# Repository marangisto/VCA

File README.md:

# VCA
DIY Modular VCA

Inspired by RJWSoft's Dual Log/Linear VCA but incorporating ideas from application notes
and use of the diode bias inputs in the OTA together with supply adjustements
to ensure both exponential and linear modes can drive levels all the way to zero.

To calibrate:

1) Set offset potentiometer so that its output viper is at 0V (measure on board).

2) Adjust the 100k trimmer (bottom-most) as close to 0mV as possible at output jack.
note that during this phase you may need to mix in adjustments of the 2k trimmer
to make this feasible.

3) Feed a 100Hz 10Vpp square signal into CV and adjust 2k trimmer (top-most) to minimize
feed-throgh on an oscilloscope.

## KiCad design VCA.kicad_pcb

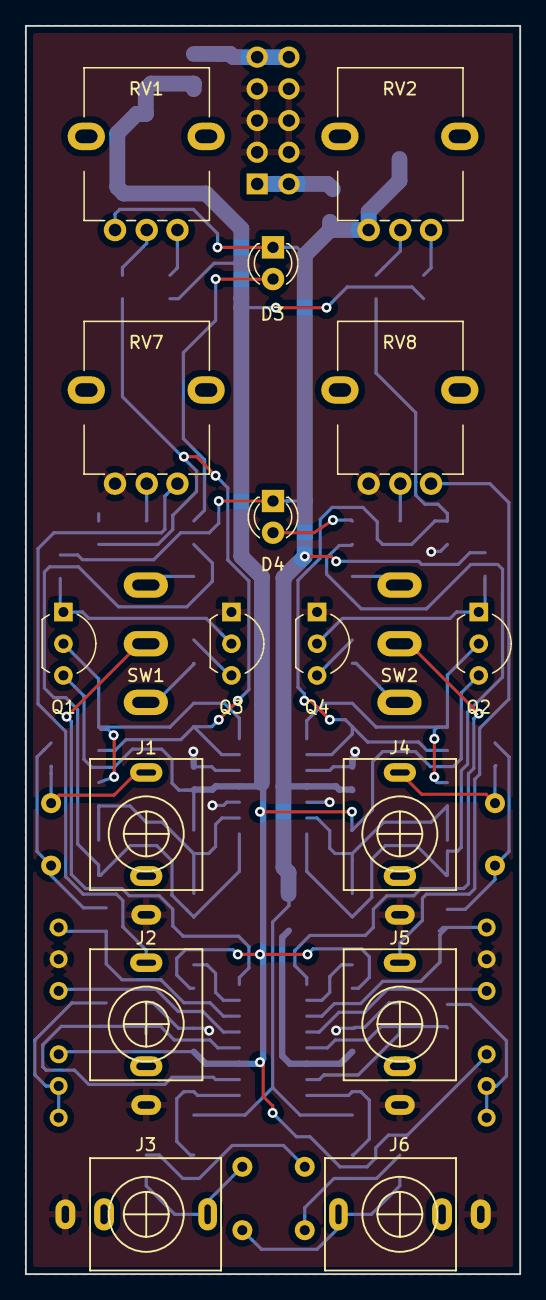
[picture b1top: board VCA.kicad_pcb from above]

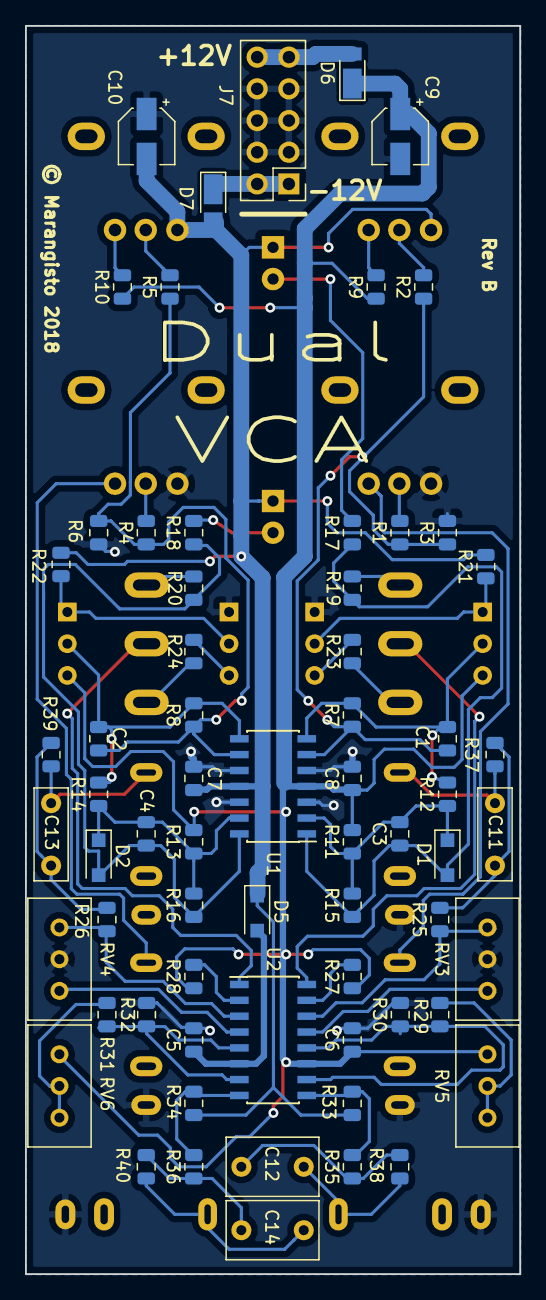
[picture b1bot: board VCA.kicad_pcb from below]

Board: 2 copper layers, 39.6 x 100.0 mm, 84 parts (66 on the bottom side), 54 nets.

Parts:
C1, C2: 2.2n; C_0805_2012Metric
C3, C4: 2,2n; C_0805_2012Metric
C5, C6, C7, C8: 100n; C_0805_2012Metric
C9, C10: 10u; CP_Elec_4x5.8
C11, C13: 220n; C_Rect_L7.2mm_W2.5mm_P5.00mm_FKS2_FKP2_MKS2_MKP2
C12, C14: 1u; C_Rect_L7.2mm_W4.5mm_P5.00mm_FKS2_FKP2_MKS2_MKP2
D1, D2, D5: 1N4148; D_SOD-123F
D3, D4: LED; LED_D3.0mm
D6, D7: DFLR1400-7; D_PowerDI-123
J1, J2, J3, J4, J5, J6: AudioJack2_Ground_Switch; PJ398SM
J7: Conn_02x05_Odd_Even; PinHeader_2x05_P2.54mm_Vertical
Q1, Q2: 2N2222; TO-92L_Inline_Wide
Q3, Q4: 2N2907; TO-92L_Inline_Wide
R1, R4: 100k; R_0805_2012Metric
R2, R5, R21, R22: 150k; R_0805_2012Metric
R3, R6, R7, R8, R33, R34: 4k7; R_0805_2012Metric
R9, R10, R15, R16: 47k; R_0805_2012Metric
R11, R13: 130k; R_0805_2012Metric
R12, R14: 680; R_0805_2012Metric
R17, R18, R35, R36: 1k; R_0805_2012Metric
R19, R20: 10k; R_0805_2012Metric
R23, R24: 9.1k; R_0805_2012Metric
R25, R26: 68k; R_0805_2012Metric
R27, R28, R30, R32: 33k; R_0805_2012Metric
R29, R31: 270k; R_0805_2012Metric
R37, R38, R39, R40: 0R; R_0805_2012Metric
RV1, RV2, RV7, RV8: 100k; AlpsRK09K
RV3, RV4: 2k; Potentiometer_Bourns_3296W_Vertical
RV5, RV6: 100k; Potentiometer_Bourns_3296W_Vertical
SW1, SW2: SW_SPDT; SP1MS1
U1: TL074; SOIC-14_3.9x8.7mm_P1.27mm
U2: LM13700; SOIC-16_3.9x9.9mm_P1.27mm

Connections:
+12V: C6.1, C8.1, C9.1, D6.1, Q1.3, Q2.3, R9.1, R10.1, R11.2, R13.2, R27.1, R28.1, RV5.1, RV6.1, U1.4, U2.11
-12V: C7.2, C10.2, D3.1, D4.1, D5.1, D7.2, R21.2, R22.2, R33.2, R34.2, RV1.3, RV2.3, U1.11
ABIA: SW1.2, U2.16
ABIB: SW2.2, U2.1
CVA: R1.2, RV7.2
CVB: R4.2, RV8.2
EXPA: R23.2, SW1.1
EXPB: R24.2, SW2.1
GND: C5.2, C6.2, C7.1, C8.2, C9.2, C10.1, J1.S, J2.S, J3.S, J4.S, J5.S, J6.S, J7.3, J7.4, J7.5, J7.6, J7.7, J7.8, Q3.1, Q4.1, R3.2, R6.2, R30.2, R32.2, RV3.2, RV4.2, RV7.3, RV8.3, U1.3, U1.5, U1.10, U1.12
INA: C11.1, R25.2, R37.1
INB: C13.1, R26.2, R39.1
LEDA: C3.1, D1.2, R15.1, R17.1, R19.2, U1.1
LEDB: C4.1, D2.2, R16.1, R18.1, R20.2, U1.14
LINA: R19.1, SW1.3
LINB: R20.1, SW2.3
unnamed: C1.1, Q1.2, R7.2, R12.2, U1.7
unnamed: C1.2, R1.1, R2.1, R3.1, R7.1, U1.6
unnamed: C2.1, Q2.2, R8.2, R14.2, U1.8
unnamed: C2.2, R4.1, R5.1, R6.1, R8.1, U1.9
unnamed: C3.2, D1.1, R11.1, R12.1, R15.2, U1.2
unnamed: C4.2, D2.1, R13.1, R14.1, R16.2, U1.13
unnamed: C5.1, D5.2, U2.6
unnamed: C11.2, J1.T, R37.2
unnamed: C12.2, J3.T, R38.2
unnamed: C13.2, J4.T, R39.2
unnamed: C14.2, J6.T, R40.2
unnamed: D3.2, R17.2
unnamed: D4.2, R18.2
unnamed: D6.2, J7.9, J7.10
unnamed: D7.1, J7.1, J7.2
unnamed: J2.T, RV7.1
unnamed: J5.T, RV8.1
unnamed: Q1.1, Q3.2, R21.1
unnamed: Q2.1, Q4.2, R22.1
unnamed: Q3.3, R23.1
unnamed: Q4.3, R24.1
unnamed: R9.2, RV1.1
unnamed: R10.2, RV2.1
unnamed: R25.1, RV3.1, U2.14
unnamed: R26.1, RV4.1, U2.3
unnamed: R27.2, U2.15
unnamed: R28.2, U2.2
unnamed: R29.1, RV5.2, RV5.3
unnamed: R29.2, R30.1, U2.10, U2.12
unnamed: R31.1, RV6.2, RV6.3
unnamed: R31.2, R32.1, U2.5, U2.7
unnamed: R33.1, R35.2, U2.9
unnamed: R34.1, R36.2, U2.8
unnamed: RV3.3, U2.13
unnamed: RV4.3, U2.4
OFFA: R2.2, RV1.2
OFFB: R5.2, RV2.2
OUTA: C12.1, R35.1, R38.1
OUTB: C14.1, R36.1, R40.1

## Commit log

2018-06-04 Added initial Spice model.
2018-06-04 Connected CV driver stage with JFET.
2018-06-07 Renamed original prototype.
2018-06-07 Hacky CircuitMaker netlist parser to attempt Spicing.
2018-06-07 Reconfigured and tuned portions of VCA-13700 in LTSpice.
2018-06-25 Some mods on spice file.
2018-06-26 Added panel drawing and rendering.
2018-06-28 Added LM13700 model (from deanm1278/LM13700-spice-model).
2018-06-28 Added stand-alone LM13700 circuit based TI datasheet but tweaked for offset control.
2018-06-28 First version of linear driver.
2018-06-29 Corrected input stage, zero offset circuit and supply bias for zero gain.
2018-06-30 Lots of tuning to line up exponential and linear profiles.
2018-06-30 More tuning, getting even amplification.
2018-06-30 Added LED indicator.
2018-06-30 Tidy up layout and use E24 resistors.
2018-07-01 Minor resistor adjustments.
2018-07-01 Change offset pot to 100k.
2018-07-01 Renamed Spice model to VCA.
2018-07-01 Added low-pass caps to op-amps.
2018-07-01 Added gerbers.
2018-07-01 Added bill-of-materials.
2018-07-01 Added some images.
2018-07-01 Component counts for 3 sets.
2018-08-09 Original design sheet.
2018-08-10 Initial version of VCA revision B, manually 'ported' from CircuitMaker.
2018-08-11 Revision B of VCA control board.
2018-08-12 Added local footprint library.
2018-08-12 Added single-board SMD design.
2018-08-12 Removed redundant split board design.
2018-08-12 Added rendering of revision B board.
2018-08-12 Moved single-board project to primary VCA design.
2018-08-12 Moved fp-lib-table.
2018-08-12 Added BOM.
2018-08-12 Generated gerbers.
2018-08-12 Avoid traces outside pour.
2018-09-15 Updaded README with calibration instructions.

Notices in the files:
VCA.kicad_pcb:
© Marangisto 2018
